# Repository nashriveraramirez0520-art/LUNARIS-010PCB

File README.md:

# LUNARIS-01 PCB 🚀

LUNARIS-01 is my first custom PCB, designed in KiCad as part of Hack Club's Starbie project.

I started by following the Starbie guide to learn the basics of schematic design, footprint assignment, PCB layout, and routing. As I worked on the board, I decided to give the project its own identity by redesigning the board outline into a spacecraft inspired by LUNARIS-01, a spaceship from another project I am developing.

## Features

- Seeed Studio XIAO ESP32-C3
- DHT11 temperature and humidity sensor
- I2C OLED display
- MPU6050 connector
- Two mechanical switches
- Custom spacecraft-shaped PCB outline
- Custom LUNARIS-01 silkscreen artwork
- Fully routed PCB with 0 unrouted connections

## Design

The schematic and PCB were designed using KiCad. During routing, I reorganized several components to make the layout work within the custom spacecraft shape.

The final board also includes a custom Saturn-inspired graphic and LUNARIS-01 branding on the silkscreen.

## Project Files

- `Starbie.kicad_sch` — Schematic
- `Starbie.kicad_pcb` — PCB layout
- `Starbie.kicad_pro` — KiCad project
- `Imported Parts.pretty/` — Custom footprints
- `Seeed_Studio_XIAO_Series.kicad_sym` — XIAO symbol library

## Status

Week 1 PCB design complete. 🚀

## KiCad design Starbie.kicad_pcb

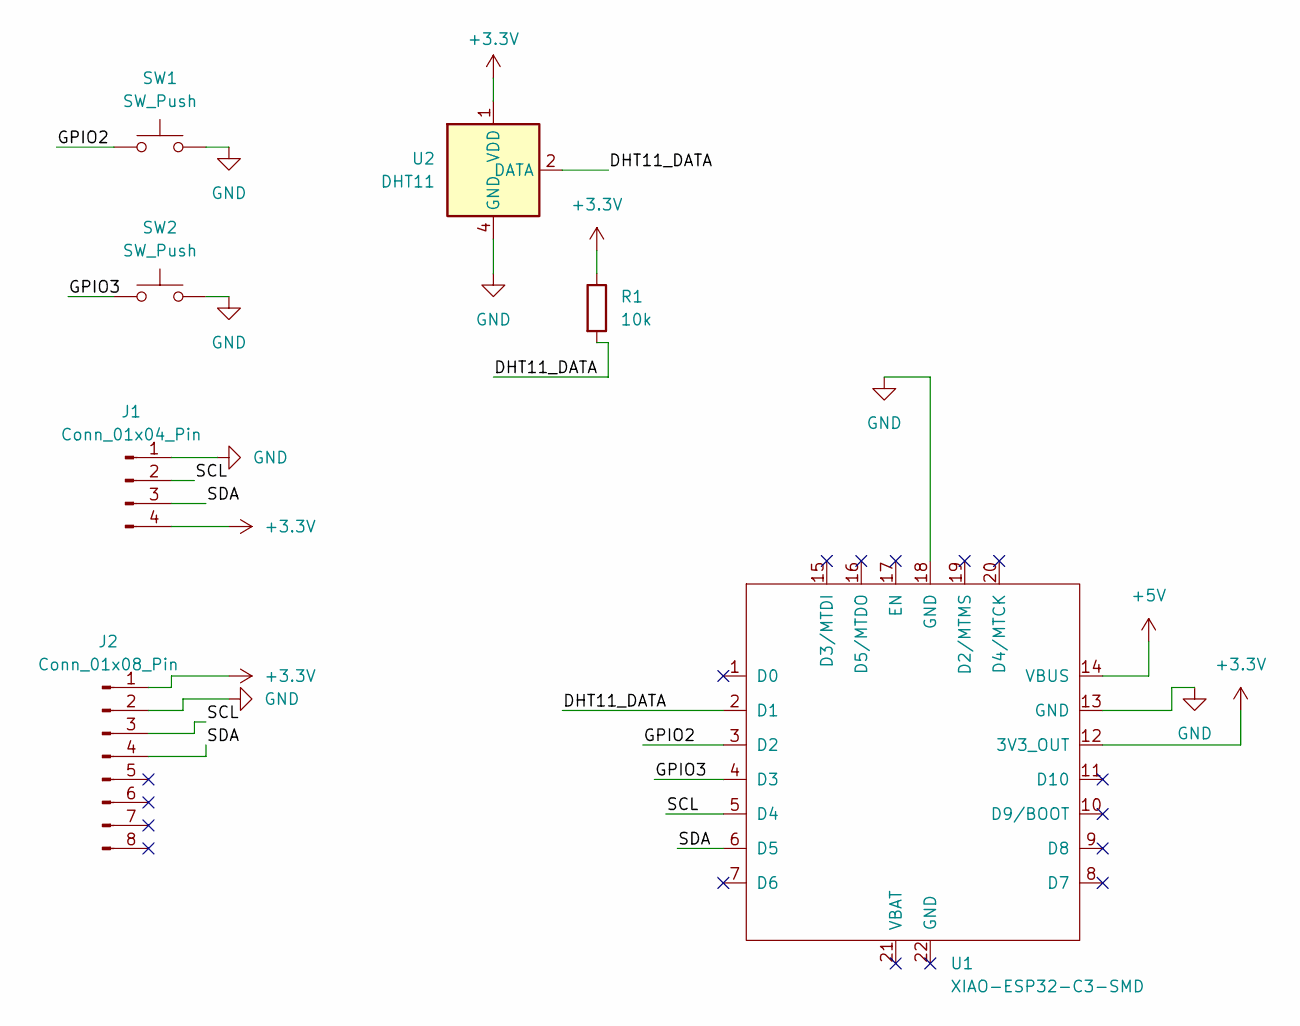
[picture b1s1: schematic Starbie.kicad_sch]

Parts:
J1: Conn_01x04_Pin; Display_128x64_096_I2C
J2: Conn_01x08_Pin; PinHeader_1x08_P2.54mm_Vertical
R1: 10k; R_Axial_DIN0204_L3.6mm_D1.6mm_P7.62mm_Horizontal
SW1, SW2: SW_Push; SW_Cherry_MX_1.00u_PCB
U1: XIAO-ESP32-C3-SMD
U2: DHT11; Aosong_DHT11_5.5x12.0_P2.54mm

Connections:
+3.3V: J1.4, J2.1, R1.1, U1.12 (3V3_OUT), U2.1 (VDD)
+5V: U1.14 (VBUS)
/DHT11_DATA: R1.2, U1.2 (D1), U2.2 (DATA)
/GPIO2: SW1.1, U1.3 (D2)
/GPIO3: SW2.1, U1.4 (D3)
/SCL: J1.2, J2.3, U1.5 (D4)
/SDA: J1.3, J2.4, U1.6 (D5)
GND: J1.1, J2.2, SW1.2, SW2.2, U1.13 (GND), U1.18 (GND), U2.4 (GND)

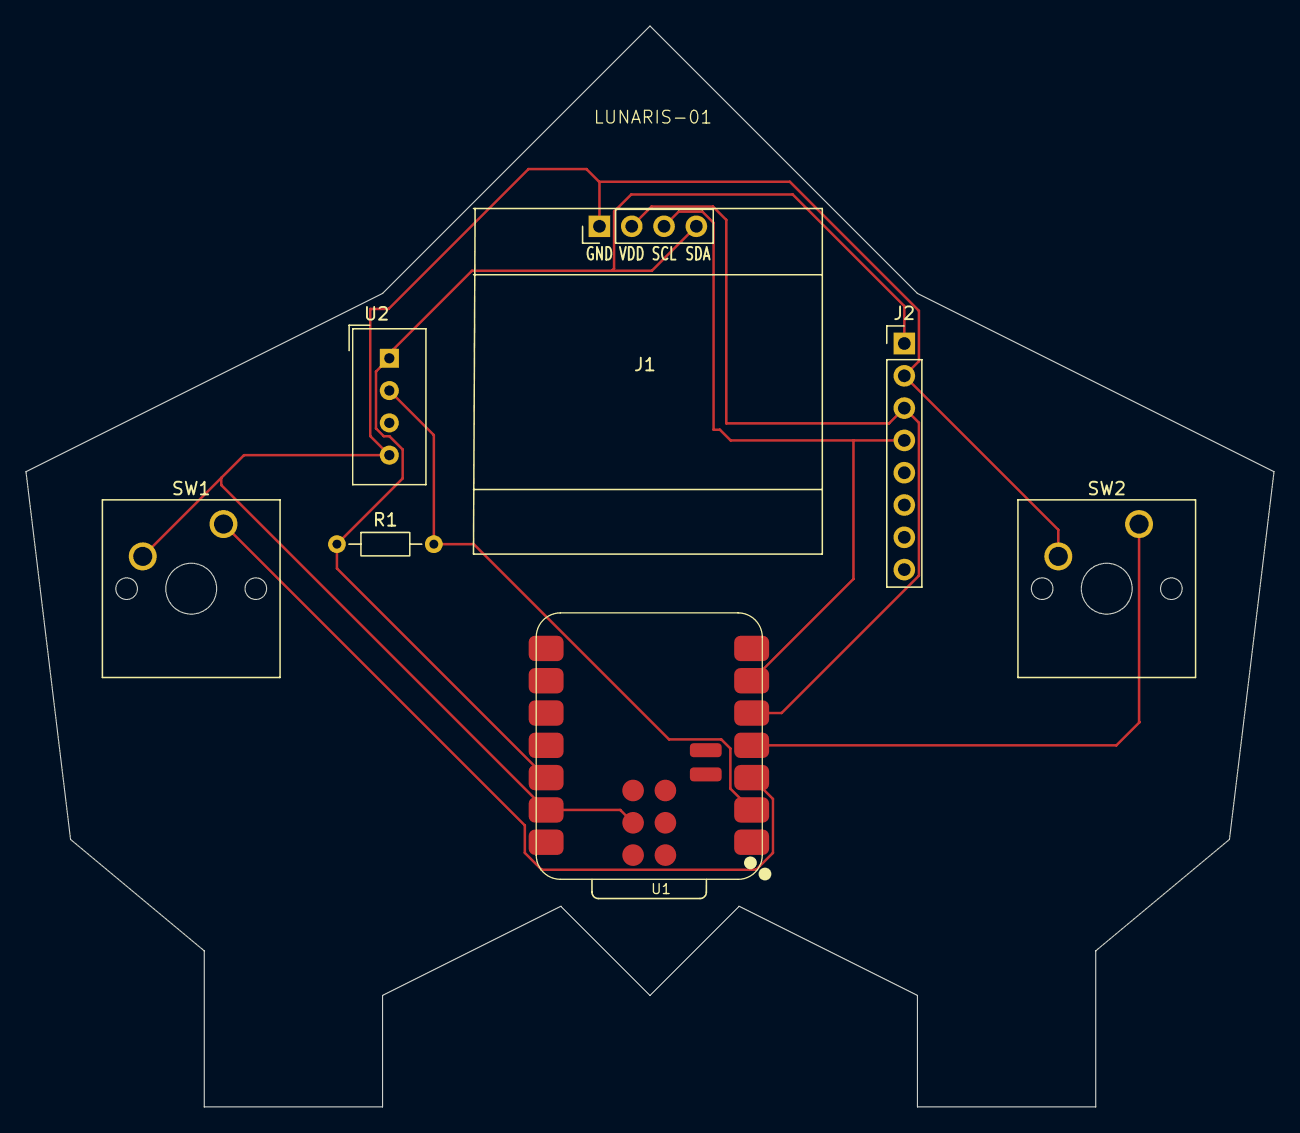
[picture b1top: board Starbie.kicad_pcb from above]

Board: 2 copper layers, 98.1 x 85.0 mm, 7 parts (0 on the bottom side), 7 nets.
